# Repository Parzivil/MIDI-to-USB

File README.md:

My Custom small form factor MIDI to USB.

I had a need to use an old piano with a midi output with my modern DAW system, so I designed this to be as low cost as possible as well as as small as posible

			Cost:	$12.00366

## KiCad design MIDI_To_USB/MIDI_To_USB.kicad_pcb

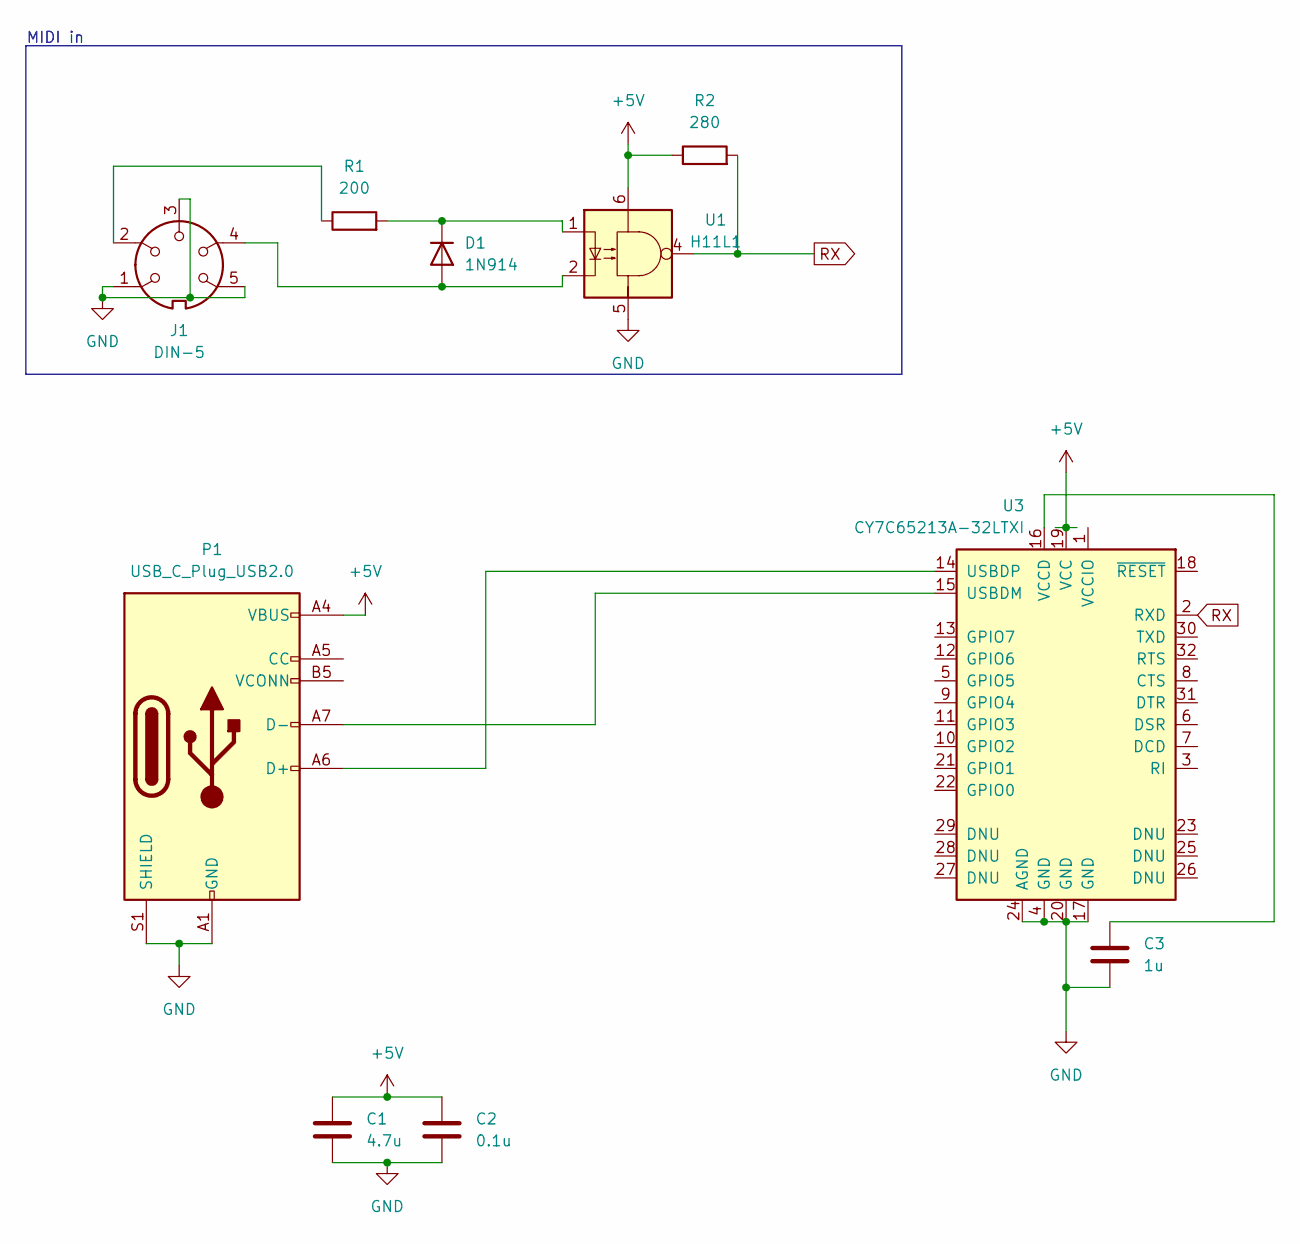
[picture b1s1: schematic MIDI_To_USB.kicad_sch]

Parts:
C1: 4.7u; C_1206_3216Metric
C2: 0.1u; C_1206_3216Metric
C3: 1u; C_1206_3216Metric
D1: 1N914; D_DO-35_SOD27_P7.62mm_Horizontal
J1: DIN-5; MIDI_DIN5
P1: USB_C_Plug_USB2.0; USB_C_Receptacle_GCT_USB4085
R1: 200; R_1206_3216Metric
R2: 280; R_1206_3216Metric
U1: H11L1; DIP-6_W7.62mm_Socket_LongPads
U3: CY7C65213A-32LTXI; QFN-32-1EP_5x5mm_P0.5mm_EP3.45x3.45mm

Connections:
+5V: C1.1, C2.1, P1.A4 (VBUS), P1.A9 (VBUS), P1.B4 (VBUS), P1.B9 (VBUS), R2.1, U1.6, U3.19 (VCC)
GND: C1.2, C2.2, C3.2, J1.1, J1.3, J1.5, P1.A1 (GND), P1.A12 (GND), P1.B1 (GND), P1.B12 (GND), P1.S1 (SHIELD), U1.5, U3.4 (GND), U3.17 (GND), U3.20 (GND), U3.24 (AGND), U3.33 (GND)
unnamed: D1.2 (A), J1.4, U1.2
unnamed: D1.1 (K), R1.2, U1.1
unnamed: J1.2, R1.1
unnamed: P1.A6 (D+), U3.14 (USBDP)
unnamed: P1.A7 (D-), U3.15 (USBDM)
unnamed: C3.1, U3.16 (VCCD)
RX: R2.2, U1.4, U3.2 (RXD)

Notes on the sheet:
MIDI in

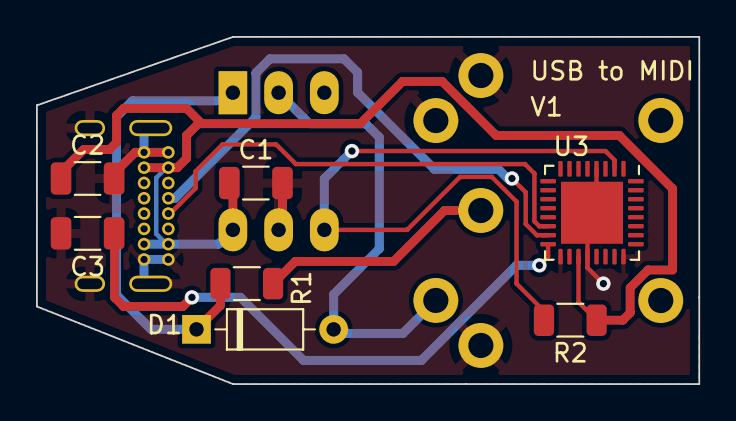
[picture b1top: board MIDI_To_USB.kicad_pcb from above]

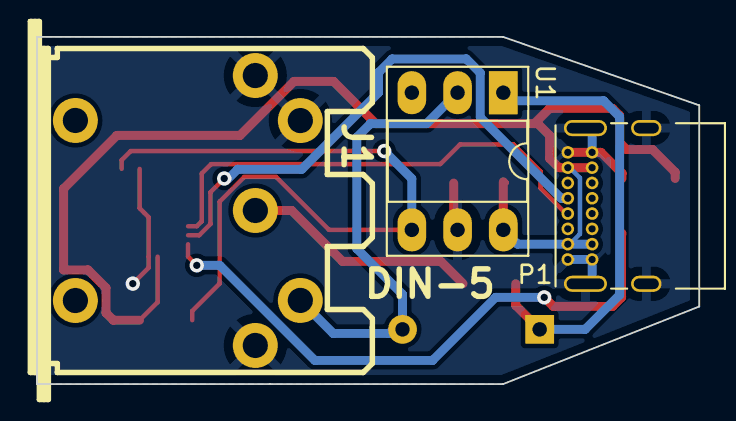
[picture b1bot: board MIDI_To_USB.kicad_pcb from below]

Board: 2 copper layers, 36.8 x 19.3 mm, 10 parts (3 on the bottom side), 9 nets.

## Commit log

2024-10-22 Setup
